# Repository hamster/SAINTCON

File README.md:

### SAINTCON Projects

You probably want to go [here](HHC/2022)

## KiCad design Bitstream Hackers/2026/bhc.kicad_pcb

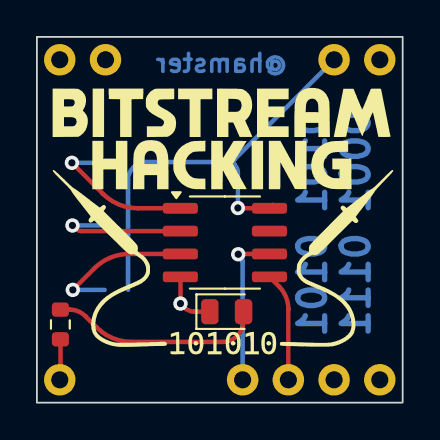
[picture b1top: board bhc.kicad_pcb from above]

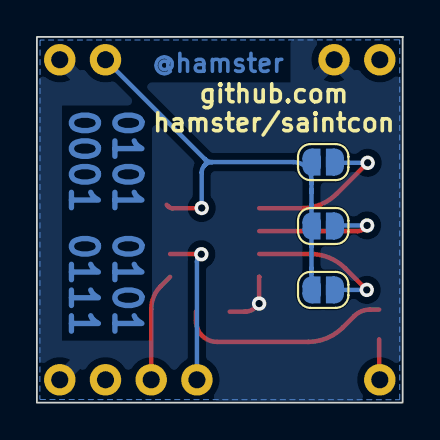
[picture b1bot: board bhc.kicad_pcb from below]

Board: 2 copper layers, 20.3 x 20.3 mm, 7 parts (3 on the bottom side), 9 nets.

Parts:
D1: LED; LED_0805_2012Metric
JP1, JP2, JP3: SolderJumper_2_Open; SolderJumper-2_P1.3mm_Open_RoundedPad1.0x1.5mm
MB1: MiniBadge_Simple; MiniBadge_Full
R1: 1k; R_0603_1608Metric
U1: AT24CS01-SSHM; SOIC-8_3.9x4.9mm_P1.27mm

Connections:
+3V3: JP1.1 (A), JP2.1 (A), JP3.1 (A), MB1.7 (+3V3), U1.8 (VCC)
GND: D1.1 (K), MB1.2 (GND), MB1.8 (GND), MB1.16 (GND), U1.4 (GND)
unnamed: D1.2 (A), R1.1
unnamed: JP1.2 (B), U1.1 (A0)
unnamed: JP2.2 (B), U1.2 (A1)
unnamed: JP3.2 (B), U1.3 (A2)
unnamed: MB1.9 (CLK), R1.2
unnamed: MB1.13 (SCL), U1.6 (SCL)
unnamed: MB1.14 (SDA), U1.5 (SDA)

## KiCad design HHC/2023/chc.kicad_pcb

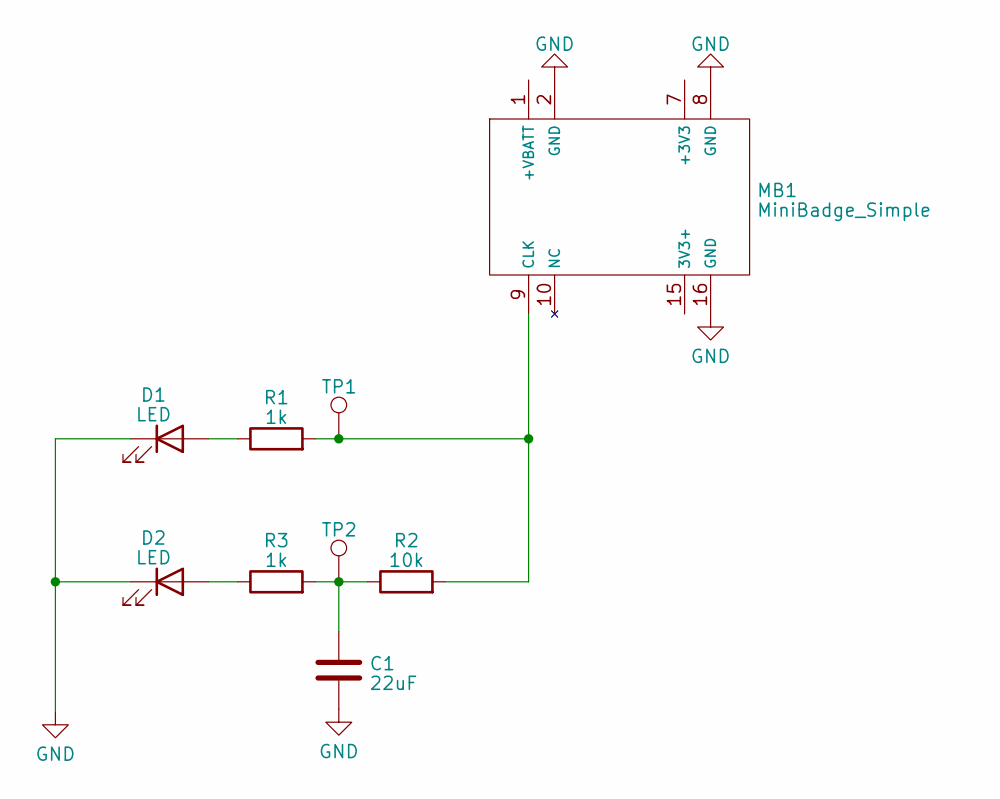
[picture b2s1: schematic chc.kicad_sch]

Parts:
C1: 22uF; C_0805_2012Metric
D1, D2: LED; LED_0805_2012Metric
MB1: MiniBadge_Simple
R1, R3: 1k; R_0603_1608Metric
R2: 10k; R_0603_1608Metric
TP1, TP2: TestPoint; TestPoint_THTPad_D1.5mm_Drill0.7mm

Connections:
GND: C1.2, D1.1 (K), D2.1 (K), MB1.2 (GND), MB1.8 (GND), MB1.16 (GND)
unnamed: C1.1, R2.1, R3.2, TP2.1
unnamed: D1.2 (A), R1.1
unnamed: D2.2 (A), R3.1
unnamed: MB1.9 (CLK), R1.2, R2.2, TP1.1

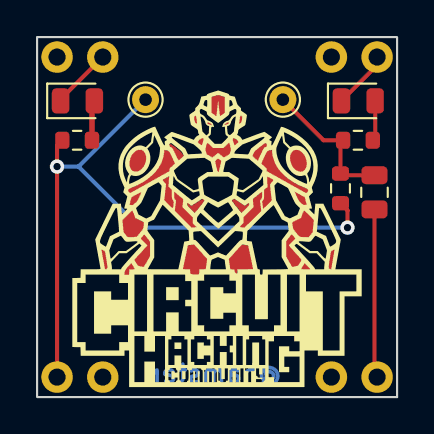
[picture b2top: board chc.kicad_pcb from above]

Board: 2 copper layers, 20.0 x 20.0 mm, 9 parts (0 on the bottom side), 5 nets.

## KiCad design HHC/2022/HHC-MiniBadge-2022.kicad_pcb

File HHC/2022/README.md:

#Hardware Hacking Community 2022
##Circuit Learning Minibadge

The goal of the minibadge this year is to provide a platform for you to learn about basic analog electronic circuits.  You'll need to acquire a kit from the HHC area, and then take it to the Solder Skills Community to assemble it.  Once you have completed that, download the circuits workbook and get started on your journey.

[Assembly Guide](assembly.md)

[Circuits Workbook](circuits-workbook.pdf)

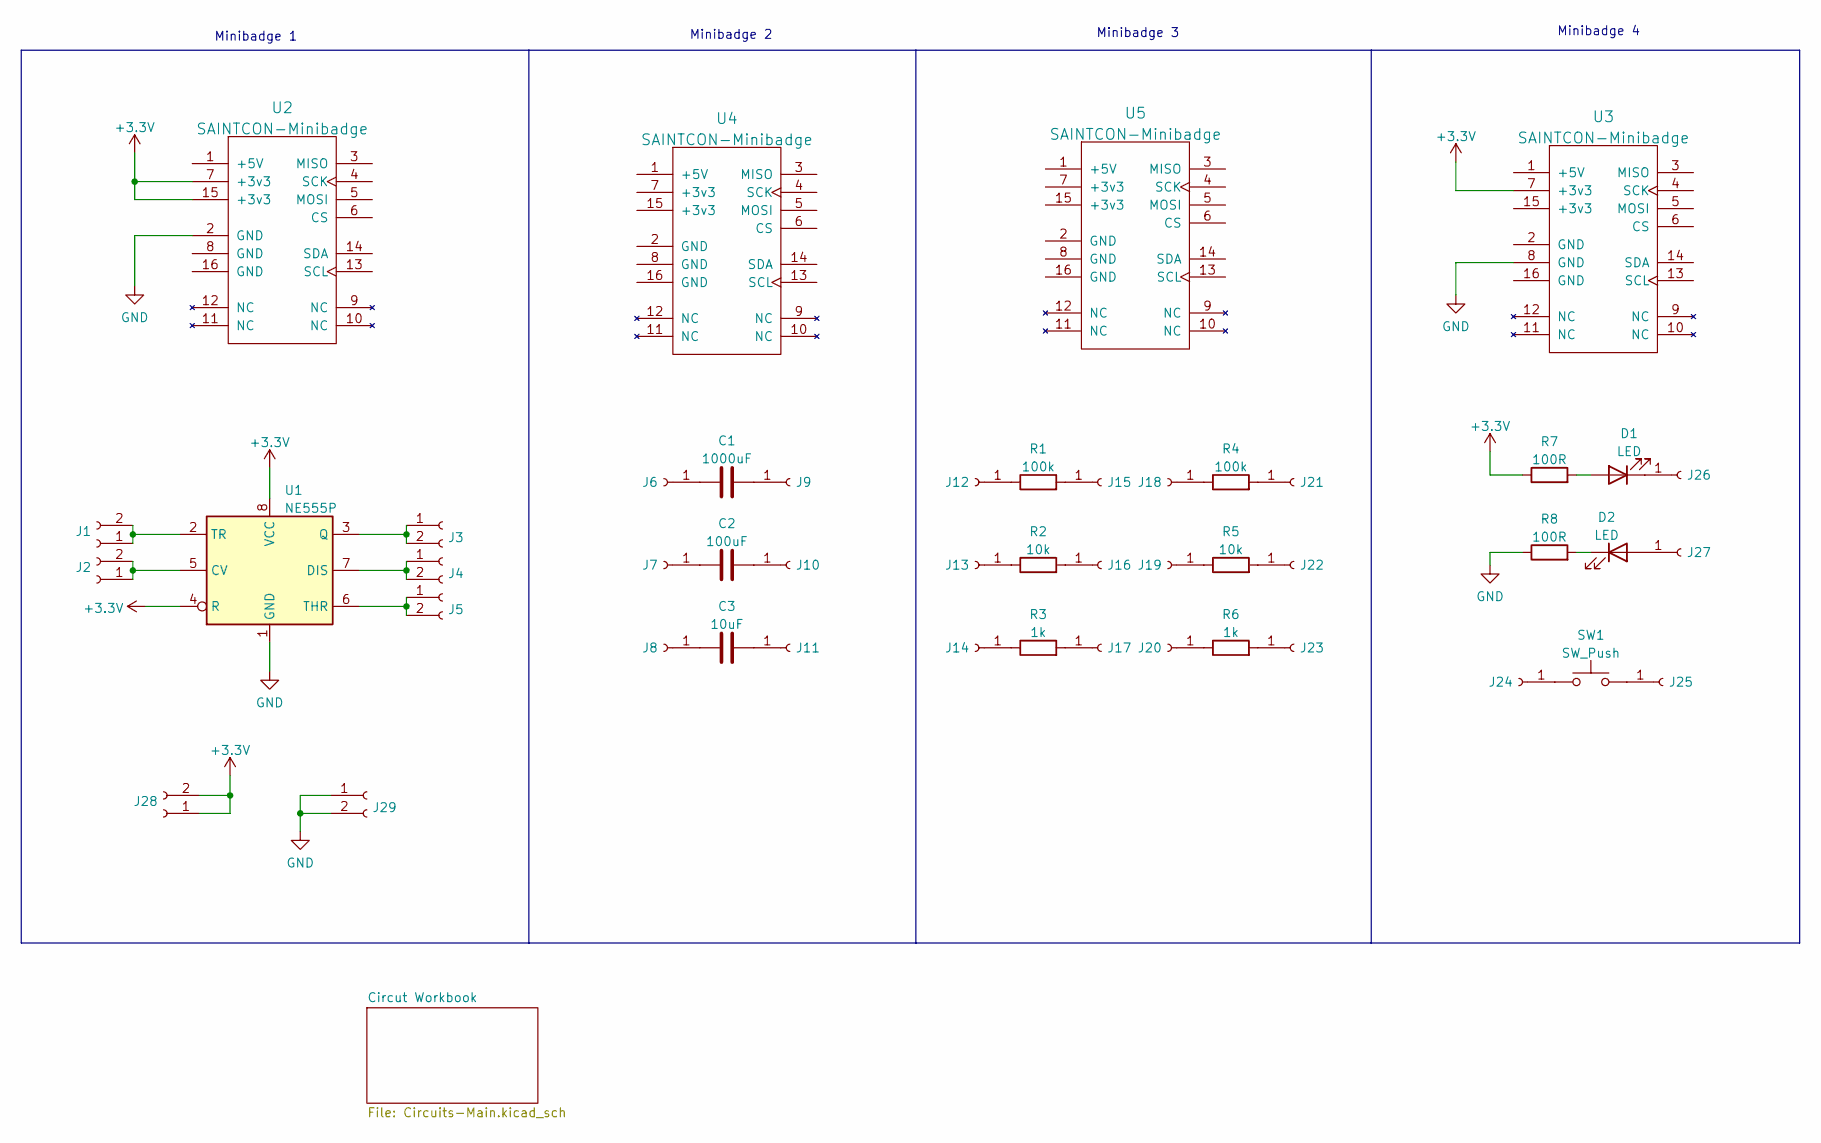
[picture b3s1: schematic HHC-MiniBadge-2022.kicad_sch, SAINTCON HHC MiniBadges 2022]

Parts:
C1: 1000uF; CP_Radial_D8.0mm_P3.50mm
C2: 100uF; CP_Radial_D5.0mm_P2.50mm
C3: 10uF; C_Disc_D5.0mm_W2.5mm_P2.50mm
D1, D2: LED; LED_D5.0mm
J1, J2, J3, J4, J5, J28, J29: Conn_01x02_Female; PinSocket_1x02_P2.54mm_Vertical
J6, J7, J8, J9, J10, J11, J12, J13, J14, J15, J16, J17, J18, J19, J20, J21, J22, J23, J24, J25, J26, J27: Conn_01x01_Female; PinSocket_1x01_P2.54mm_Vertical
R1, R4: 100k; R_Axial_DIN0204_L3.6mm_D1.6mm_P2.54mm_Vertical
R2, R5: 10k; R_Axial_DIN0204_L3.6mm_D1.6mm_P2.54mm_Vertical
R3, R6: 1k; R_Axial_DIN0204_L3.6mm_D1.6mm_P2.54mm_Vertical
R7, R8: 100R; R_Axial_DIN0204_L3.6mm_D1.6mm_P2.54mm_Vertical
SW1: SW_Push; SW_PUSH_6mm_H7.3mm
U1: NE555P; DIP-8_W7.62mm
U2, U3, U4, U5: SAINTCON-Minibadge; SAINTCON-Minibadge-PowerOnly-Silk

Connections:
+3.3V: J28.1, J28.2, R7.1, U1.4 (R), U1.8 (VCC), U2.7 (+3v3), U2.15 (+3v3), U3.7 (+3v3)
GND: J29.1, J29.2, R8.1, U1.1 (GND), U2.2 (GND), U3.8 (GND)
unnamed: C1.1, J6.1
unnamed: C1.2, J9.1
unnamed: C2.1, J7.1
unnamed: C2.2, J10.1
unnamed: C3.1, J8.1
unnamed: C3.2, J11.1
unnamed: D1.1 (K), J26.1
unnamed: D1.2 (A), R7.2
unnamed: D2.1 (K), R8.2
unnamed: D2.2 (A), J27.1
unnamed: J1.1, J1.2, U1.2 (TR)
unnamed: J2.1, J2.2, U1.5 (CV)
unnamed: J3.1, J3.2, U1.3 (Q)
unnamed: J4.1, J4.2, U1.7 (DIS)
unnamed: J5.1, J5.2, U1.6 (THR)
unnamed: J12.1, R1.1
unnamed: J13.1, R2.1
unnamed: J14.1, R3.1
unnamed: J15.1, R1.2
unnamed: J16.1, R2.2
unnamed: J17.1, R3.2
unnamed: J18.1, R4.1
unnamed: J19.1, R5.1
unnamed: J20.1, R6.1
unnamed: J21.1, R4.2
unnamed: J22.1, R5.2
unnamed: J23.1, R6.2
unnamed: J24.1, SW1.1
unnamed: J25.1, SW1.2

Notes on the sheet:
Minibadge 4
Minibadge 3
Minibadge 2
Minibadge 1

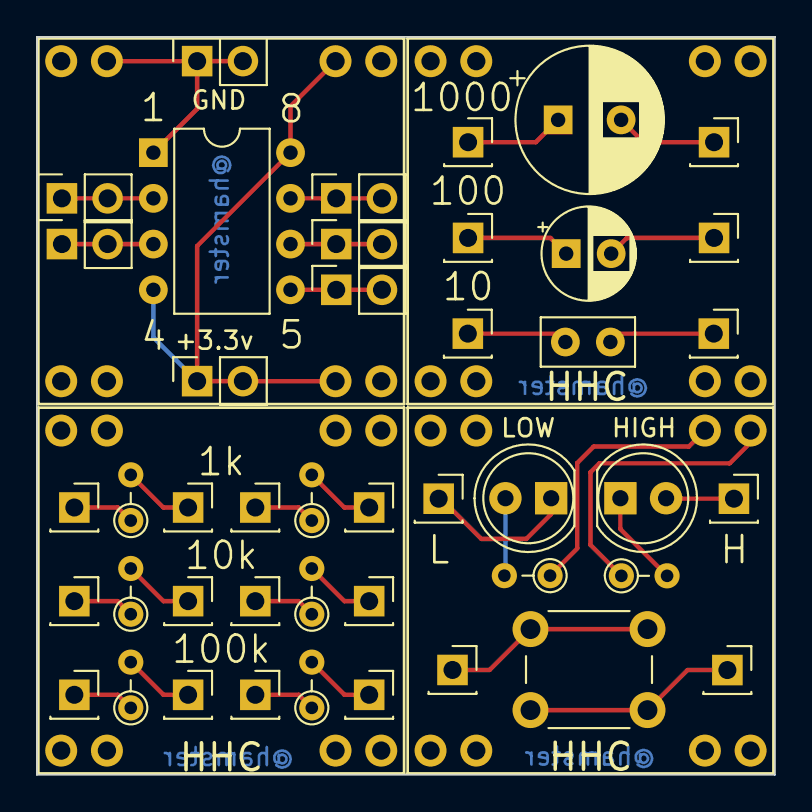
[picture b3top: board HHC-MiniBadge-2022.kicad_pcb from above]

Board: 2 copper layers, 41.0 x 41.0 mm, 48 parts (0 on the bottom side), 31 nets.

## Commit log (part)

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2022-09-26 Adding rev 1.0 of the hardware design
2022-10-24 Adding assembly guide
2022-10-24 Fixing some formatting
2022-10-24 More corrections
2022-10-25 Adding circuits workbook
2022-10-26 Adding link to assembly video and fixing resistor colors
2023-09-01 Adding the 2023 minibadge
2023-09-02 Added panel for the 2023 minibadge
2023-09-02 Renamed HHC to CHC
2025-08-07 Adding bitstream hackers minibadge design
